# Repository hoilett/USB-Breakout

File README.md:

# USB-Breakout
USB Breakout board for probing USB devices. USB A male (to computer) to USB A female (to peripheral)

Hello world!

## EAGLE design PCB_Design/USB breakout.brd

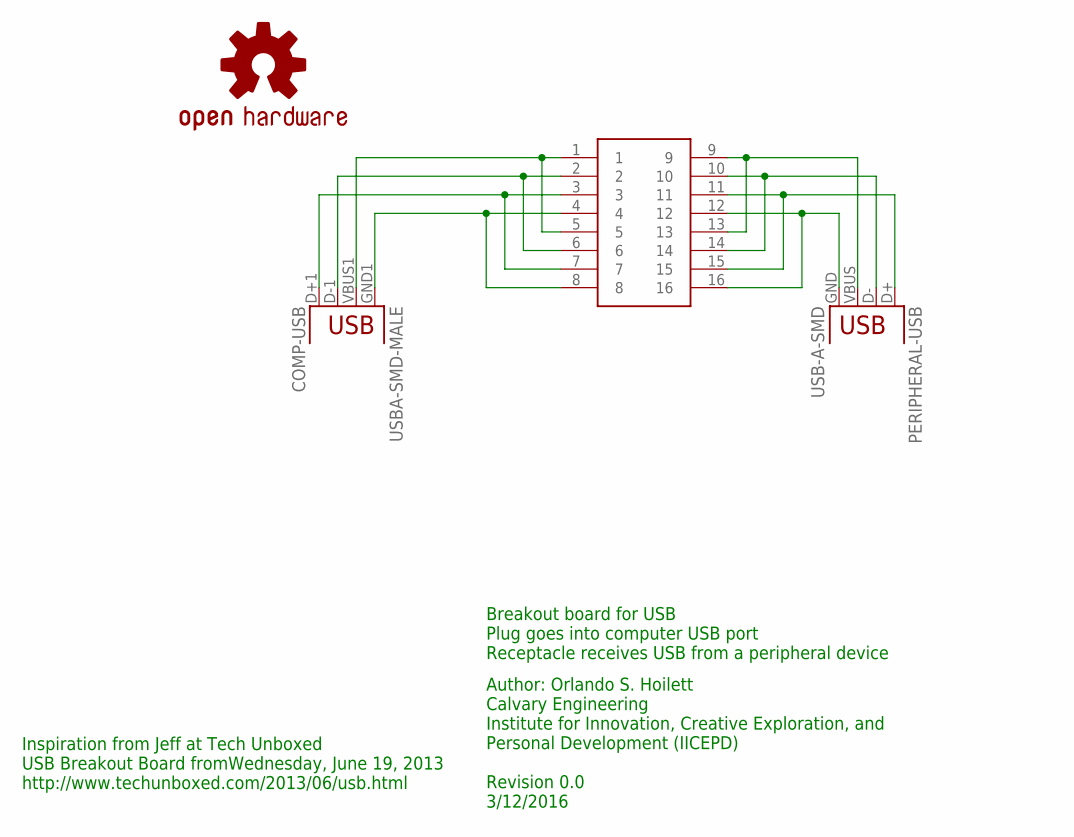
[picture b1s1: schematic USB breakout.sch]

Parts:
COMP-USB: USBA-SMD-MALE; USB-A-SMT-MALE
LOGO1: OSHW-LOGOS; OSHW-LOGO-S
PERIPHERAL-USB: USB-A-SMD; USB-A-S-NOSILK-FEMALE
U$1: MX4X4; M04X4

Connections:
C-D+: COMP-USB.D+1 (D+), U$1.3, U$1.7
C-D-: COMP-USB.D-1 (D-), U$1.2, U$1.6
C-GND: COMP-USB.GND1 (GND), U$1.4, U$1.8
C-V+: COMP-USB.VBUS1 (VBUS), U$1.1, U$1.5
P-D+: PERIPHERAL-USB.D+, U$1.11, U$1.15
P-D-: PERIPHERAL-USB.D-, U$1.10, U$1.14
P-GND: PERIPHERAL-USB.GND, U$1.12, U$1.16
P-V+: PERIPHERAL-USB.VBUS, U$1.9, U$1.13

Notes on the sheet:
Author: Orlando S. Hoilett Calvary Engineering Institute for Innovation, Creative Exploration, and Personal Development (IICEPD) Revision 0.0 3/12/2016
Inspiration from Jeff at Tech Unboxed USB Breakout Board fromWednesday, June 19, 2013 http://www.techunboxed.com/2013/06/usb.html
Breakout board for USB Plug goes into computer USB port Receptacle receives USB from a peripheral device

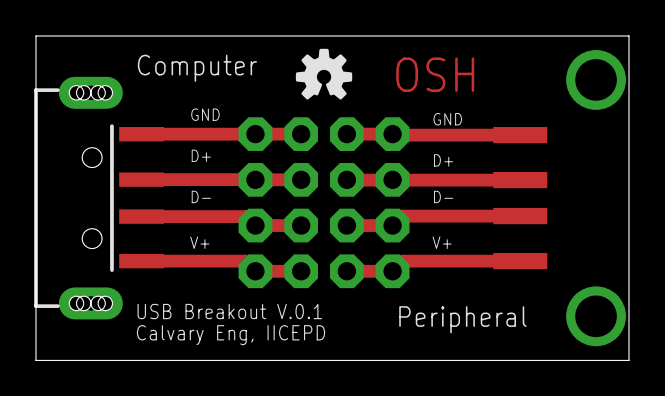
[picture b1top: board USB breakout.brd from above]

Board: 2 copper layers, 32.9 x 18.0 mm, 4 parts (0 on the bottom side), 8 nets.

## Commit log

2016-05-02 Added files via upload

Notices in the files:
parts and their libraries:
SparkFun-Connectors: Licensing: Creative Commons ShareAlike 4.0 International - https://creativecommons.org/licenses/by-sa/4.0
